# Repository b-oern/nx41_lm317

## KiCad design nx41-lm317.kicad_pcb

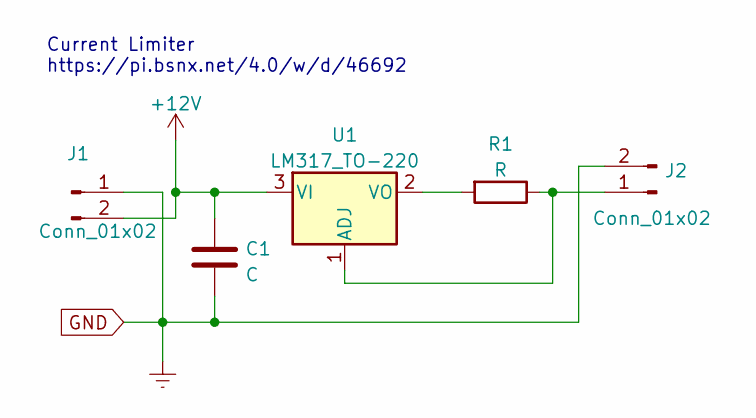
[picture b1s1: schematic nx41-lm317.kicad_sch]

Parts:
C1: C; CP_Radial_D5.0mm_P2.50mm
J1, J2: Conn_01x02; TerminalBlock_bornier-2_P5.08mm
R1: R; R_Axial_DIN0414_L11.9mm_D4.5mm_P5.08mm_Vertical
U1: LM317_TO-220; TO-220-3_Vertical

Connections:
+12V: C1.1, J1.2, U1.3 (VI)
GND: C1.2, J1.1, J2.2
unnamed: J2.1, R1.1, U1.1 (ADJ)
unnamed: R1.2, U1.2 (VO)

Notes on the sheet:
Current Limiter https://pi.bsnx.net/4.0/w/d/46692

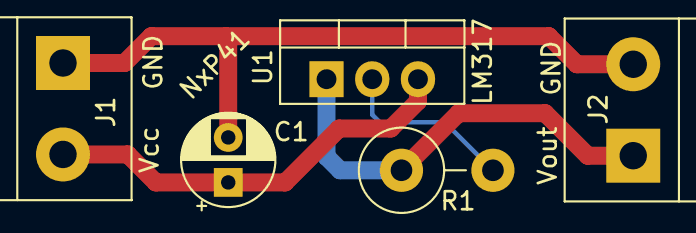
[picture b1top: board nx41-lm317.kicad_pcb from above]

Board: 2 copper layers, 5 parts (0 on the bottom side), 4 nets.

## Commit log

2026-01-16 init
2026-03-06 Platine
